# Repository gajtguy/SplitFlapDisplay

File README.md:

# Split-Flap Display

A modular, 3D-printed split-flap display controllable over RS485 from a Raspberry Pi. Each module holds 64 characters and modules can be chained together to build a display of any width.

**YouTube Build Video:** https://www.youtube.com/watch?v=-C8_AtxEEQc

---

## How It Works

Each module contains:
- A 3D-printed drum that holds 64 individual flaps (one per character)
- A stepper motor driving the drum through a gear train
- A Hall effect sensor for homing
- A custom driver PCB (ATtiny1616 + RS485 transceiver + ULN2003 stepper driver)

Modules communicate over a shared RS485 bus. A Raspberry Pi running a Python web interface sends commands over USB-RS485 to each module individually by address.

---

## Repository Structure

```
CAD/                              - 3D printable parts (Bambu Lab profiles included)
SplitFlapDriverATtiny1616 V2 KiCad/  - Driver PCB KiCad that I used in the video, for my build
SplitFlapDriverATtiny1616V3       - Updated Driver PCB KiCad project, which should be slightly cheaper to manufacture
SplitFlapBusBoard KiCad/          - Bus board KiCad project
SplitFlapFirmware/                - Arduino firmware for the PCBs
SplitFlap-RPI-FRONTEND/           - Raspberry Pi Python web frontend
Reference Docs/                   - Component datasheets
BOM.md                            - Bill of materials

**OnShape Model:** https://cad.onshape.com/documents/87c916b33ca5d6492b457485/w/b3e5f0f05f6619e6e7931347/e/582ef2164e20b0aa994708ab

---

## Parts List

See [BOM.md](BOM.md) for the complete bill of materials, broken into three sections:

- **PCB / Electronics** — all SMD components with JLCPCB part numbers for easy ordering
- **Module BOM** — 3D printed parts and hardware per module, with quantities scaled to 45 modules
- **Other Components** — system-level parts (Raspberry Pi, power supply, C14 connector, etc.)

---

## Ordering the PCB from JLCPCB

The driver board is designed to be ordered from JLCPCB with their PCB Assembly (PCBA) service so the SMD components arrive pre-soldered.

### Step 1 — Export Gerbers from KiCad

1. Open the project in `SplitFlapDriverATtiny1616 V2 KiCad/`
2. In KiCad PCB editor, go to **File → Fabrication Outputs → Gerbers**
3. Export to a folder, then zip the contents
4. Also export the drill file from the same menu

Alternatively, pre-exported Gerber and PCBA files are already be present in the KiCad project folder.

### Step 2 — Upload to JLCPCB

1. Go to [jlcpcb.com](https://jlcpcb.com) and click **Order Now**
2. Upload the Gerber zip file
3. Set your desired quantity (minimum 5)
4. Leave most settings at default; adjust PCB colour if desired

### Step 3 — Enable PCB Assembly (PCBA)

1. Toggle **PCB Assembly** on
2. Select **Standard PCBA** and set the assembly side to **Top Side**
3. Click **Confirm**

### Step 4 — Upload BOM and CPL Files

1. Upload the **BOM file** from the KiCad project folder — this maps component values to JLCPCB part numbers. The part numbers in `BOM.md` match what is in this file.
2. Upload the **CPL (Component Placement List)** file — this tells JLCPCB where each component sits on the board
3. Review the component matches on the next screen. All parts should auto-match using the C-numbers in [BOM.md](BOM.md). Confirm any that need manual review.

### Step 5 — Review and Order

1. Check the parts list — confirm quantities and part numbers match the [BOM.md](BOM.md) PCB section
2. Proceed through the review screens and place your order

> **Note:** A few through-hole parts (pin headers, JST connectors) are not included in PCBA. These are listed in the BOM and will need to be soldered by hand.

---

## 3D Printing

All printable files are in the `CAD/` folder. A Bambu Lab print profile is included in `CAD/64FlapsWithLetters/` for the flaps. Print the flaps in the correct colour for each character — see the video for details on the full 64-character set.

Parts per module:
- Enclosure Body, Right Cover, Left Cover
- Drum Body, Drum Cap
- Motor Gear, Center Gear, Gear Plate
- DIN Rail Mount, Wire Retainer
- 64 Flaps

---

## Firmware

Located in `SplitFlapFirmware/`. The firmware is Arduino-based and targets the ATtiny1616.

- Flash via UPDI programmer (see https://github.com/SpenceKonde/AVR-Guidance/blob/master/UPDI/jtag2updi.md if you need to make one)
- Each module needs a unique address (0–44) stored in EEPROM. Be sure to edit this between flashes.

---

## Frontend

Located in `SplitFlap-RPI-FRONTEND/`. A Python web interface running on a Raspberry Pi sends display commands over USB-RS485 at 115200 baud.

Need a USB-serial dongle. I used this one: https://www.adafruit.com/product/5994

---

## License

This project is licensed under [Creative Commons Attribution-NonCommercial-ShareAlike 4.0 International (CC BY-NC-SA 4.0)](https://creativecommons.org/licenses/by-nc-sa/4.0/).

You are free to share and adapt this project for non-commercial purposes, as long as you give appropriate credit to Adam G Makes and distribute any derivatives under the same license.

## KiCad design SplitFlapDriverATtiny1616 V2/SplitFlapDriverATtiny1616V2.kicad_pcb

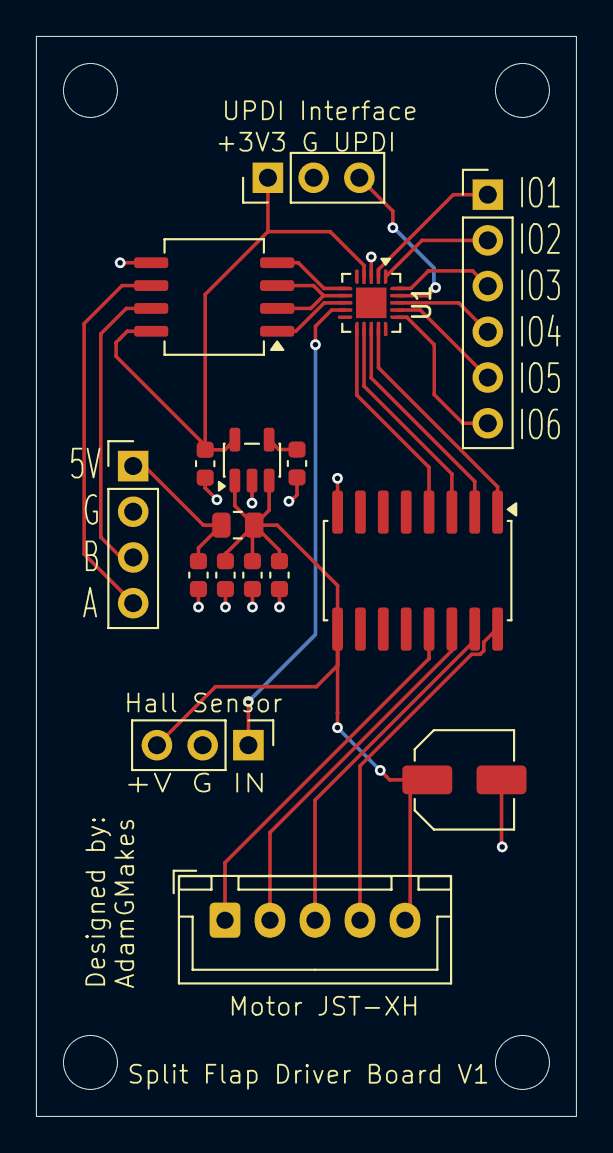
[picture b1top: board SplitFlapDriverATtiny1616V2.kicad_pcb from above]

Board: 2 copper layers, 30.0 x 60.0 mm, 17 parts (0 on the bottom side), 26 nets.

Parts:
C1: 100u; C_Elec_5x5.4
C2, C3, C6: 470n; C_0603_1608Metric
C4, C5: 10u; C_0603_1608Metric
C7: 100n; C_0603_1608Metric
J1: UPDI Programming; PinHeader_1x03_P2.54mm_Vertical
J2: BUS POGO; PinHeader_1x04_P2.54mm_Vertical
J3: Stepper Connector; JST_XH_B5B-XH-A_1x05_P2.50mm_Vertical
J4: Hall Effect; PinHeader_1x03_P2.54mm_Vertical
J5: Conn_01x06_Pin; PinHeader_1x06_P2.54mm_Vertical
R1: 0R; R_0805_2012Metric
U1: ATtiny1616-MNR; VQFN-20-1EP_3x3mm_P0.4mm_EP1.7x1.7mm
U2: ULN2003ADR; SOIC-16W_5.3x10.2mm_P1.27mm
U3: SN65HVD72DR; SOIC-8_5.3x6.2mm_P1.27mm
U5: SPX3819M5-L-3-3; SOT-23-5

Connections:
+3V3: C5.1, J1.1, U1.4 (VCC), U3.8 (VCC), U5.5 (OUT)
+VBUS: C2.1, J2.1, R1.1
+VBUSF: C1.1, C3.1, C4.1, C7.1, J3.5, J4.3, R1.2, U2.9 (COM), U5.1 (IN), U5.3 (EN)
DE/RE: U1.7 (PA6), U3.2 (~RE), U3.3 (DE)
GND: C1.2, C2.2, C3.2, C4.2, C5.2, C6.2, C7.2, J1.2, J2.2, J4.2, U1.3 (GND), U2.8 (GND), U3.5 (GND), U5.2 (GND)
HALL_IN: J4.1, U1.9 (PB5)
IO1: J5.1, U1.2 (EXTCLK/PA3)
IO2: J5.2, U1.1 (PA2)
IO3: J5.3, U1.20 (PA1)
IO4: J5.4, U1.18 (PC3)
IO5: J5.5, U1.17 (PC2)
IO6: J5.6, U1.16 (PC1)
M1: J3.4, U2.16 (O1)
M2: J3.3, U2.15 (O2)
M3: J3.2, U2.14 (O3)
M4: J3.1, U2.13 (O4)
unnamed: C6.1, U5.4 (BP)
RS465_A: J2.4, U3.6 (A)
RS465_B: J2.3, U3.7 (B)
RXD: U1.8 (PA7), U3.1 (R)
TXD: U1.6 (PA5), U3.4 (D)
ULN_IN1: U1.14 (PB0), U2.1 (I1)
ULN_IN2: U1.13 (PB1), U2.2 (I2)
ULN_IN3: U1.12 (PB2/TOSC2), U2.3 (I3)
ULN_IN4: U1.11 (PB3/TOSC1), U2.4 (I4)
UPDI: J1.3, U1.19 (~RESET/PA0/UPDI)

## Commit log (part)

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2025-11-13 Finished SplitFlapDriverATTiny1616 and sent for production
2025-12-10 Updated Hall Effect Header to JST-PH
2026-04-24 Cleaned up repo for sharing
2026-04-25 Add BOM.md and README.md documentation
2026-04-27 Add OnShape model link to README
